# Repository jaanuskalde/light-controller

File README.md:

light-controller
================

Tech-thing 32 channel mains light dimmer.

Version 1.0 has some mains clearance problems, handle with care.

http://jaanus.tech-thing.org

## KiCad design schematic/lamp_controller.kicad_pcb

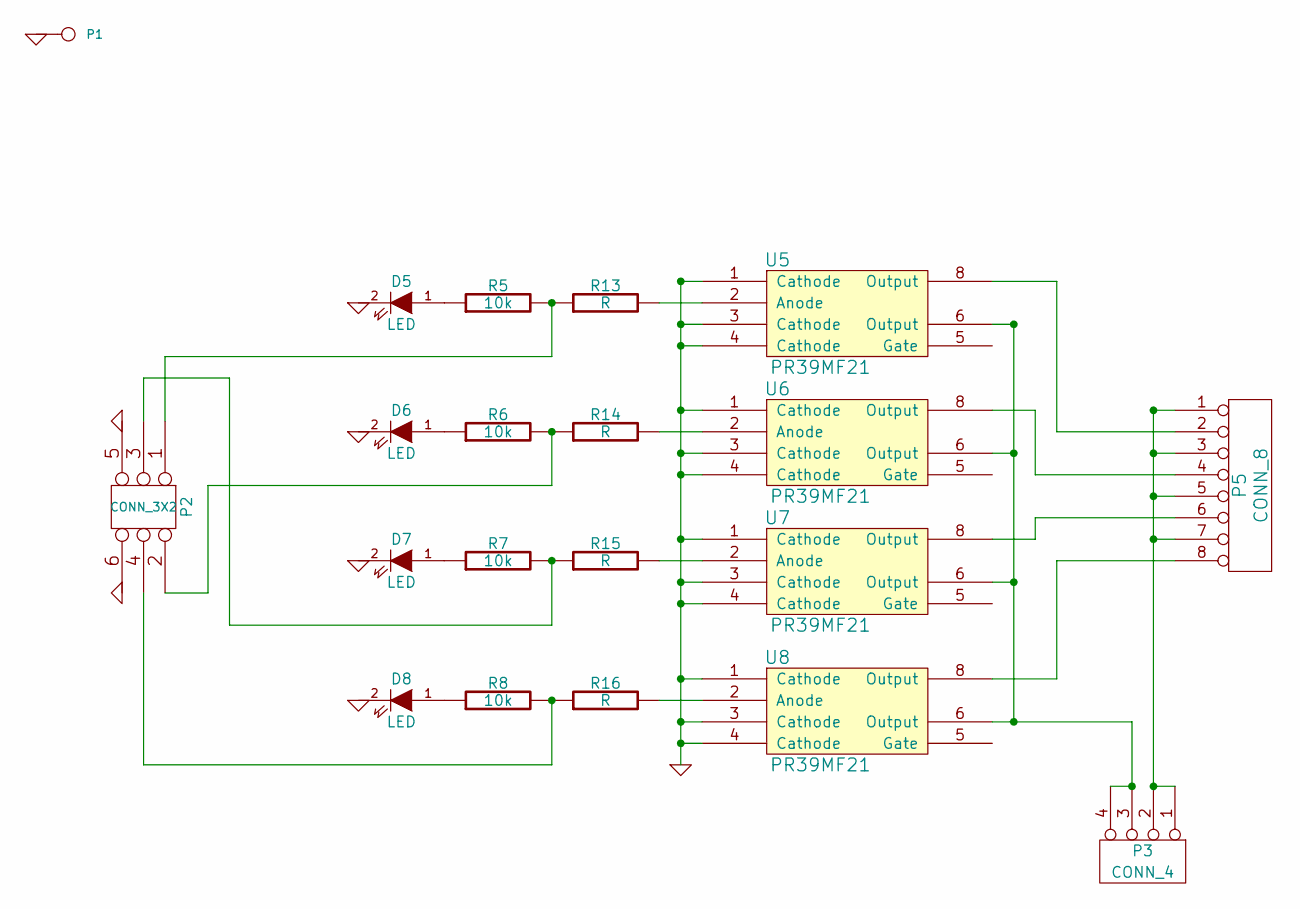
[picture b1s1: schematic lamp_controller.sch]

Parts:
D5, D6, D7, D8: LED
P1: CONN_1
P2: CONN_3X2
P3: CONN_4
P5: CONN_8
R5, R6, R7, R8: 10k
R13, R14, R15, R16: R
U5, U6, U7, U8: PR39MF21

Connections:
GND: D5.2 (K), D6.2 (K), D7.2 (K), D8.2 (K), P1.1, P2.5, P2.6, U5.1 (Cathode), U5.3 (Cathode), U5.4 (Cathode), U6.1 (Cathode), U6.3 (Cathode), U6.4 (Cathode), U7.1 (Cathode), U7.3 (Cathode), U7.4 (Cathode), U8.1 (Cathode), U8.3 (Cathode), U8.4 (Cathode)
unnamed: P5.4, U6.8 (Output)
unnamed: P5.6, U7.8 (Output)
unnamed: P5.8, U8.8 (Output)
unnamed: P3.3, P3.4, U5.6 (Output), U6.6 (Output), U7.6 (Output), U8.6 (Output)
unnamed: P2.2, R6.2, R14.1
unnamed: P2.3, R7.2, R15.1
unnamed: P2.4, R8.2, R16.1
unnamed: R13.2, U5.2 (Anode)
unnamed: R14.2, U6.2 (Anode)
unnamed: R15.2, U7.2 (Anode)
unnamed: R16.2, U8.2 (Anode)
unnamed: P2.1, R5.2, R13.1
unnamed: P5.2, U5.8 (Output)
unnamed: P3.1, P3.2, P5.1, P5.3, P5.5, P5.7
unnamed: D7.1 (A), R7.1
unnamed: D8.1 (A), R8.1
unnamed: D5.1 (A), R5.1
unnamed: D6.1 (A), R6.1

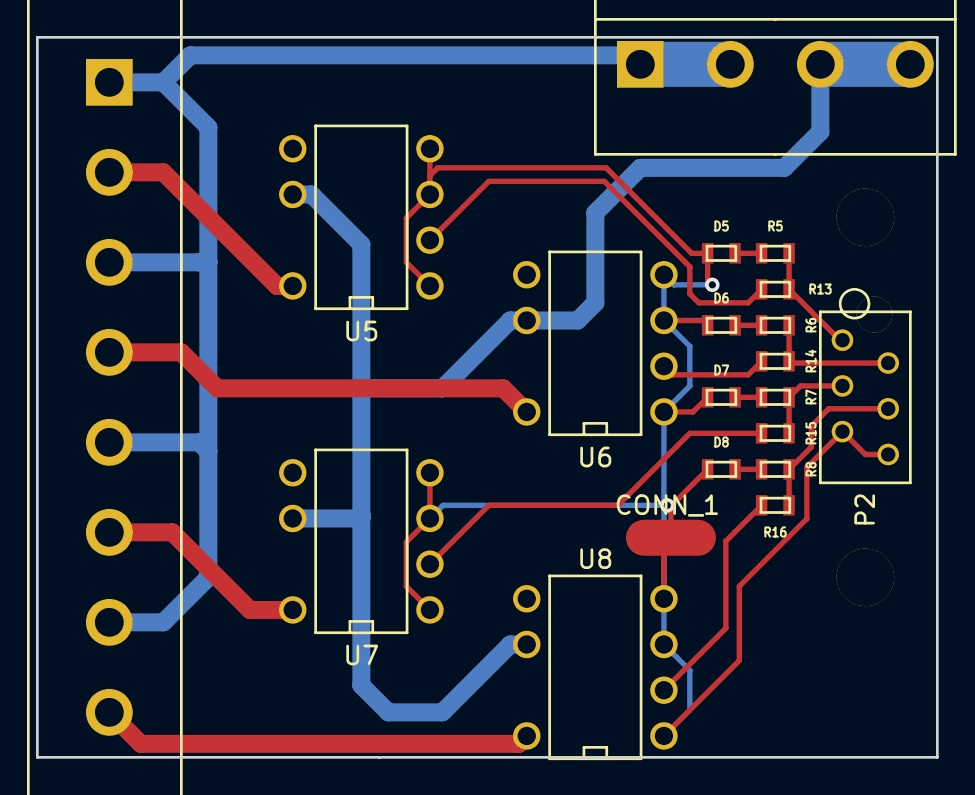
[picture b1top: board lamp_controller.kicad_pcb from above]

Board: 2 copper layers, 50.0 x 40.0 mm, 23 parts (0 on the bottom side), 19 nets.

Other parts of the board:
drill_2mm: VAL**; drill_2mm
drill_3.2mm, drill_3.2mm#2: VAL**; drill_3.2mm

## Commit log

2014-05-21 Project version 1.0
2014-05-21 Warning to readme
